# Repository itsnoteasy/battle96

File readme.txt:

this is a work in progress keyboard, not ready for use in a build.

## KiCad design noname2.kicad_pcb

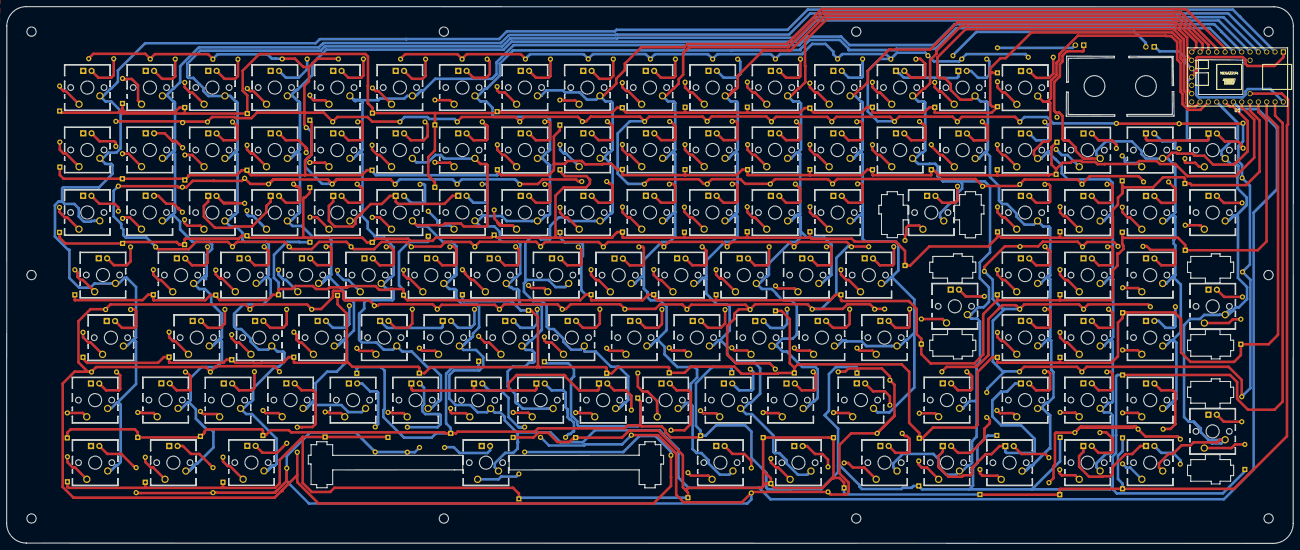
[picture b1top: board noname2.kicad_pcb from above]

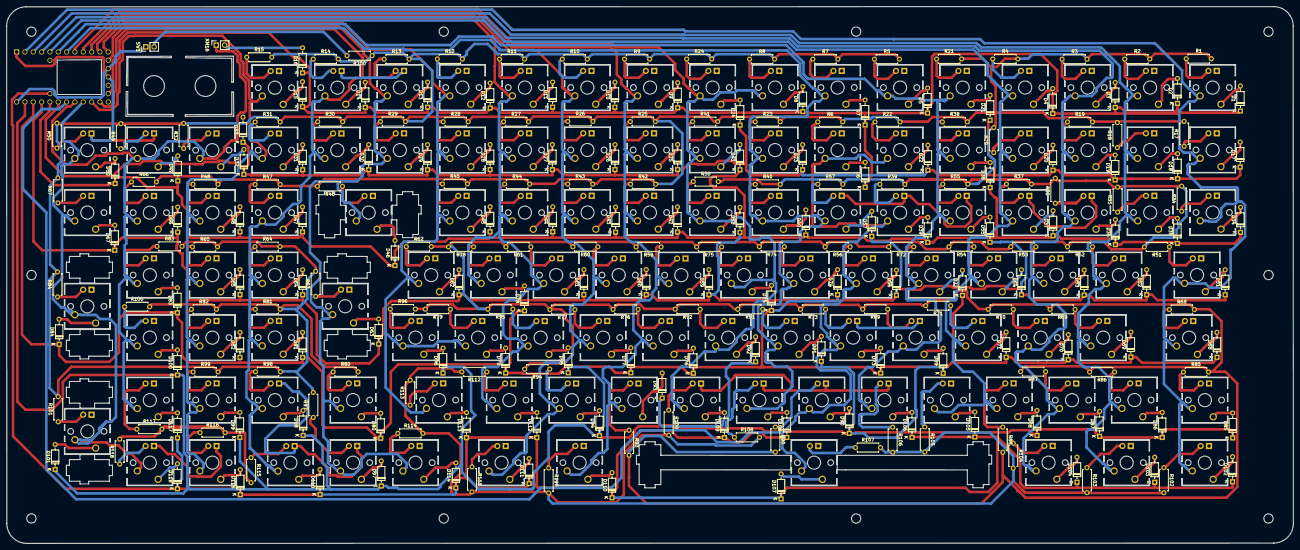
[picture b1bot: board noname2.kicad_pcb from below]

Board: 2 copper layers, 392.1 x 163.5 mm, 354 parts (237 on the bottom side), 262 nets.

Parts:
D1, D2, D3, D4, D5, D6, D7, D8, D9, D10, D11, D12, D13, D14, D15, D16, D17, D18, D19, D20, D21, D22, D23, D24, D25, D26, D27, D28, D29, D30, D31, D32, D33, D34, D35, D36, D37, D38, D39, D40, D41, D42, D43, D44, D45, D46, D47, D48, D49, D50, D51, D52, D53, D54, D55, D56, D57, D58, D59, D60, D61, D62, D63, D64, D65, D66, D67, D68, D69, D70, D71, D72, D73, D74, D75, D76, D77, D78, D79, D80, D81, D82, D83, D84, D85, D86, D87, D88, D89, D90, D91, D92, D93, D94, D95, D96, D97, D98, D99, D100, D101, D102, D103, D104, D105, D106, D107, D108, D109, D110, D111, D112, D113, D114, D115, D116, D117, D118: 1N4148; D_DO-35_SOD27_P7.62mm_Horizontal
MX1, MX2, MX3, MX4, MX5, MX6, MX7, MX8, MX9, MX10, MX11, MX12, MX13, MX14, MX15, MX17, MX18, MX19, MX20, MX21, MX22, MX23, MX24, MX25, MX26, MX27, MX28, MX29, MX30, MX31, MX32, MX34, MX35, MX36, MX37, MX38, MX39, MX40, MX41, MX42, MX43, MX44, MX45, MX46, MX47, MX48, MX49, MX50, MX51, MX52, MX53, MX54, MX55, MX56, MX57, MX58, MX59, MX60, MX61, MX62, MX63, MX64, MX65, MX66, MX67, MX68, MX69, MX70, MX71, MX72, MX73, MX74, MX75, MX76, MX77, MX78, MX79, MX80, MX81, MX82, MX83, MX84, MX85, MX86, MX87, MX88, MX89, MX90, MX91, MX92, MX93, MX94, MX95, MX96, MX97, MX98, MX99, MX100, MX101, MX102, MX103, MX104, MX105, MX106, MX107, MX108, MX109, MX110, MX111, MX112, MX113, MX114, MX115, MX116, MX117, MX118: MX-1U; MX_breakout2
R1, R2, R3, R4, R5, R6, R7, R8, R9, R10, R11, R12, R13, R14, R15, R17, R18, R19, R20, R21, R22, R23, R24, R25, R26, R27, R28, R29, R30, R31, R32, R34, R35, R36, R37, R38, R39, R40, R41, R42, R43, R44, R45, R46, R47, R48, R49, R50, R51, R52, R53, R54, R55, R56, R57, R58, R59, R60, R61, R62, R63, R64, R65, R66, R67, R68, R69, R70, R71, R72, R73, R74, R75, R76, R77, R78, R79, R80, R81, R82, R83, R84, R85, R86, R87, R88, R89, R90, R91, R92, R93, R94, R95, R96, R97, R98, R99, R100, R101, R102, R103, R104, R105, R106, R107, R108, R109, R110, R111, R112, R113, R114, R115, R116, R117, R118, R200: R; R_Axial_DIN0207_L6.3mm_D2.5mm_P7.62mm_Horizontal
SW1: SW_SPST; PinHeader_1x02_P2.54mm_Vertical
U1: TEENSY2.0; Teensy2.0
XM16: Conn_01x02_Male; PinSocket_1x02_P2.54mm_Vertical

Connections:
COL0: MX1.1, MX17.1, MX34.1, MX51.1, MX68.1, MX85.1, MX102.1, U1.2
COL1: MX2.1, MX18.1, MX35.1, MX52.1, MX69.1, MX86.1, MX103.1, U1.3
COL2: MX3.1, MX19.1, MX36.1, MX53.1, MX70.1, MX87.1, MX104.1, U1.4
COL3: MX4.1, MX20.1, MX37.1, MX54.1, MX71.1, MX88.1, MX105.1, U1.5
COL4: MX5.1, MX21.1, MX38.1, MX55.1, MX72.1, MX89.1, MX106.1, U1.6
COL5: MX6.1, MX22.1, MX39.1, MX56.1, MX73.1, MX90.1, MX107.1, U1.23
COL6: MX7.1, MX23.1, MX40.1, MX57.1, MX74.1, MX91.1, MX108.1, U1.7
COL7: MX8.1, MX24.1, MX41.1, MX58.1, MX75.1, MX92.1, MX109.1, U1.8
COL8: MX9.1, MX25.1, MX42.1, MX59.1, MX76.1, MX93.1, MX110.1, U1.9
COL9: MX10.1, MX26.1, MX43.1, MX60.1, MX77.1, MX94.1, MX111.1, U1.10
COL10: MX11.1, MX27.1, MX44.1, MX61.1, MX78.1, MX95.1, MX112.1, U1.11
COL11: MX12.1, MX28.1, MX45.1, MX62.1, MX79.1, MX96.1, MX113.1, U1.12
COL12: MX13.1, MX29.1, MX46.1, MX63.1, MX80.1, MX97.1, MX114.1, U1.13
COL13: MX14.1, MX30.1, MX47.1, MX64.1, MX81.1, MX98.1, MX115.1, U1.17
COL14: MX15.1, MX31.1, MX48.1, MX65.1, MX82.1, MX99.1, MX116.1, U1.20
COL15: MX32.1, MX49.1, MX66.1, MX83.1, MX100.1, MX117.1, U1.22, XM16.1
COL16: MX50.1, MX67.1, MX84.1, MX101.1, MX118.1, U1.21
GND: MX1.4, MX2.4, MX3.4, MX4.4, MX5.4, MX6.4, MX7.4, MX8.4, MX9.4, MX10.4, MX11.4, MX12.4, MX13.4, MX14.4, MX15.4, MX17.4, MX18.4, MX19.4, MX20.4, MX21.4, MX22.4, MX23.4, MX24.4, MX25.4, MX26.4, MX27.4, MX28.4, MX29.4, MX30.4, MX31.4, MX32.4, MX34.4, MX35.4, MX36.4, MX37.4, MX38.4, MX39.4, MX40.4, MX41.4, MX42.4, MX43.4, MX44.4, MX45.4, MX46.4, MX47.4, MX48.4, MX49.4, MX50.4, MX51.4, MX52.4, MX53.4, MX54.4, MX55.4, MX56.4, MX57.4, MX58.4, MX59.4, MX60.4, MX61.4, MX62.4, MX63.4, MX64.4, MX65.4, MX66.4, MX67.4, MX68.4, MX69.4, MX70.4, MX71.4, MX72.4, MX73.4, MX74.4, MX75.4, MX76.4, MX77.4, MX78.4, MX79.4, MX80.4, MX81.4, MX82.4, MX83.4, MX84.4, MX85.4, MX86.4, MX87.4, MX88.4, MX89.4, MX90.4, MX91.4, MX92.4, MX93.4, MX94.4, MX95.4, MX96.4, MX97.4, MX98.4, MX99.4, MX100.4, MX101.4, MX102.4, MX103.4, MX104.4, MX105.4, MX106.4, MX107.4, MX108.4, MX109.4, MX110.4, MX111.4, MX112.4, MX113.4, MX114.4, MX115.4, MX116.4, MX117.4, MX118.4, U1.1, U1.15
unnamed: D1.2, MX1.2
unnamed: D2.2, MX2.2
unnamed: D3.2, MX3.2
unnamed: D4.2, MX4.2
unnamed: D5.2, MX5.2
unnamed: D6.2, MX6.2
unnamed: D7.2, MX7.2
unnamed: D8.2, MX8.2
unnamed: D9.2, MX9.2
unnamed: D10.2, MX10.2
unnamed: D11.2, MX11.2
unnamed: D12.2, MX12.2
unnamed: D13.2, MX13.2
unnamed: D14.2, MX14.2
unnamed: D15.2, MX15.2
unnamed: D16.2, XM16.2
unnamed: D17.2, MX17.2
unnamed: D18.2, MX18.2
unnamed: D19.2, MX19.2
unnamed: D20.2, MX20.2
unnamed: D21.2, MX21.2
unnamed: D22.2, MX22.2
unnamed: D23.2, MX23.2
unnamed: D24.2, MX24.2
unnamed: D25.2, MX25.2
unnamed: D26.2, MX26.2
unnamed: D27.2, MX27.2
unnamed: D28.2, MX28.2
unnamed: D29.2, MX29.2
unnamed: D30.2, MX30.2
unnamed: D31.2, MX31.2
unnamed: D32.2, MX32.2
unnamed: D34.2, MX34.2
unnamed: D35.2, MX35.2
unnamed: D36.2, MX36.2
unnamed: D37.2, MX37.2
unnamed: D38.2, MX38.2
unnamed: D39.2, MX39.2
unnamed: D40.2, MX40.2
unnamed: D41.2, MX41.2
unnamed: D42.2, MX42.2
unnamed: D43.2, MX43.2
unnamed: D44.2, MX44.2
unnamed: D45.2, MX45.2
unnamed: D46.2, MX46.2
unnamed: D47.2, MX47.2
unnamed: D48.2, MX48.2
unnamed: D49.2, MX49.2
unnamed: D50.2, MX50.2
unnamed: D51.2, MX51.2
unnamed: D52.2, MX52.2
unnamed: D53.2, MX53.2
unnamed: D54.2, MX54.2
unnamed: D55.2, MX55.2
unnamed: D56.2, MX56.2
unnamed: D57.2, MX57.2
unnamed: D58.2, MX58.2
unnamed: D59.2, MX59.2
unnamed: D60.2, MX60.2
unnamed: D61.2, MX61.2
unnamed: D62.2, MX62.2
unnamed: D63.2, MX63.2
unnamed: D64.2, MX64.2
unnamed: D65.2, MX65.2
unnamed: D66.2, MX66.2
unnamed: D67.2, MX67.2
unnamed: D68.2, MX68.2
unnamed: D69.2, MX69.2
unnamed: D70.2, MX70.2
unnamed: D71.2, MX71.2
unnamed: D72.2, MX72.2
unnamed: D73.2, MX73.2
unnamed: D74.2, MX74.2
unnamed: D75.2, MX75.2
unnamed: D76.2, MX76.2
unnamed: D77.2, MX77.2
unnamed: D78.2, MX78.2
unnamed: D79.2, MX79.2
unnamed: D80.2, MX80.2
unnamed: D81.2, MX81.2
unnamed: D82.2, MX82.2
unnamed: D83.2, MX83.2
unnamed: D84.2, MX84.2
unnamed: D85.2, MX85.2
unnamed: D86.2, MX86.2
unnamed: D87.2, MX87.2
unnamed: D88.2, MX88.2
unnamed: D89.2, MX89.2
unnamed: D90.2, MX90.2
unnamed: D91.2, MX91.2
unnamed: D92.2, MX92.2
unnamed: D93.2, MX93.2
unnamed: D94.2, MX94.2
unnamed: D95.2, MX95.2
unnamed: D96.2, MX96.2
unnamed: D97.2, MX97.2
unnamed: D98.2, MX98.2
unnamed: D99.2, MX99.2
unnamed: D100.2, MX100.2
unnamed: D101.2, MX101.2
unnamed: D102.2, MX102.2
unnamed: D103.2, MX103.2
unnamed: D104.2, MX104.2
unnamed: D105.2, MX105.2
unnamed: D106.2, MX106.2
unnamed: D107.2, MX107.2
unnamed: D108.2, MX108.2
unnamed: D109.2, MX109.2
unnamed: D110.2, MX110.2
unnamed: D111.2, MX111.2
unnamed: D112.2, MX112.2
unnamed: D113.2, MX113.2
unnamed: D114.2, MX114.2
unnamed: D115.2, MX115.2
unnamed: D116.2, MX116.2
unnamed: D117.2, MX117.2
unnamed: D118.2, MX118.2
unnamed: MX1.3, R1.1
unnamed: MX2.3, R2.1
unnamed: MX3.3, R3.1
unnamed: MX4.3, R4.1
unnamed: MX5.3, R5.1
unnamed: MX6.3, R6.1
unnamed: MX7.3, R7.1
unnamed: MX8.3, R8.1
unnamed: MX9.3, R9.1
unnamed: MX10.3, R10.1
unnamed: MX11.3, R11.1
unnamed: MX12.3, R12.1
unnamed: MX13.3, R13.1
unnamed: MX14.3, R14.1
unnamed: MX15.3, R15.1
unnamed: MX17.3, R17.1
unnamed: MX18.3, R18.1
unnamed: MX19.3, R19.1
unnamed: MX20.3, R20.1
unnamed: MX21.3, R21.1
unnamed: MX22.3, R22.1
unnamed: MX23.3, R23.1
unnamed: MX24.3, R24.1
unnamed: MX25.3, R25.1
unnamed: MX26.3, R26.1
unnamed: MX27.3, R27.1
unnamed: MX28.3, R28.1
unnamed: MX29.3, R29.1
unnamed: MX30.3, R30.1
unnamed: MX31.3, R31.1
unnamed: MX32.3, R32.1
unnamed: MX34.3, R34.1
unnamed: MX35.3, R35.1
unnamed: MX36.3, R36.1
unnamed: MX37.3, R37.1
unnamed: MX38.3, R38.1
unnamed: MX39.3, R39.1
unnamed: MX40.3, R40.1
unnamed: MX41.3, R41.1
unnamed: MX42.3, R42.1
unnamed: MX43.3, R43.1
unnamed: MX44.3, R44.1
unnamed: MX45.3, R45.1
unnamed: MX46.3, R46.1
unnamed: MX47.3, R47.1
unnamed: MX48.3, R48.1
unnamed: MX49.3, R49.1
unnamed: MX50.3, R50.1
unnamed: MX51.3, R51.1
unnamed: MX52.3, R52.1
unnamed: MX53.3, R53.1
unnamed: MX54.3, R54.1
unnamed: MX55.3, R55.1
unnamed: MX56.3, R56.1
unnamed: MX57.3, R57.1
unnamed: MX58.3, R58.1
unnamed: MX59.3, R59.1
unnamed: MX60.3, R60.1
unnamed: MX61.3, R61.1
unnamed: MX62.3, R62.1
unnamed: MX63.3, R63.1
unnamed: MX64.3, R64.1
unnamed: MX65.3, R65.1
unnamed: MX66.3, R66.1
unnamed: MX67.3, R67.1
unnamed: MX68.3, R68.1
unnamed: MX69.3, R69.1
unnamed: MX70.3, R70.1
unnamed: MX71.3, R71.1
unnamed: MX72.3, R72.1
unnamed: MX73.3, R73.1
unnamed: MX74.3, R74.1
unnamed: MX75.3, R75.1
unnamed: MX76.3, R76.1
unnamed: MX77.3, R77.1
unnamed: MX78.3, R78.1
unnamed: MX79.3, R79.1
unnamed: MX80.3, R80.1
unnamed: MX81.3, R81.1
unnamed: MX82.3, R82.1
unnamed: MX83.3, R83.1
unnamed: MX84.3, R84.1
unnamed: MX85.3, R85.1
unnamed: MX86.3, R86.1
unnamed: MX87.3, R87.1
unnamed: MX88.3, R88.1
unnamed: MX89.3, R89.1
unnamed: MX90.3, R90.1
unnamed: MX91.3, R91.1
unnamed: MX92.3, R92.1
unnamed: MX93.3, R93.1
unnamed: MX94.3, R94.1
unnamed: MX95.3, R95.1
unnamed: MX96.3, R96.1
unnamed: MX97.3, R97.1
unnamed: MX98.3, R98.1
unnamed: MX99.3, R99.1
unnamed: MX100.3, R100.1
unnamed: MX101.3, R101.1
unnamed: MX102.3, R102.1
unnamed: MX103.3, R103.1
unnamed: MX104.3, R104.1
unnamed: MX105.3, R105.1
unnamed: MX106.3, R106.1
unnamed: MX107.3, R107.1
unnamed: MX108.3, R108.1
unnamed: MX109.3, R109.1
unnamed: MX110.3, R110.1
unnamed: MX111.3, R111.1
unnamed: MX112.3, R112.1
unnamed: MX113.3, R113.1
unnamed: MX114.3, R114.1
unnamed: MX115.3, R115.1
unnamed: MX116.3, R116.1
unnamed: MX117.3, R117.1
unnamed: MX118.3, R118.1
unnamed: R1.2, R2.2, R3.2, R4.2, R5.2, R6.2, R7.2, R8.2, R9.2, R10.2, R11.2, R12.2, R13.2, R14.2, R15.2, R17.2, R18.2, R19.2, R20.2, R21.2, R22.2, R23.2, R24.2, R25.2, R26.2, R27.2, R28.2, R29.2, R30.2, R31.2, R32.2, R34.2, R35.2, R36.2, R37.2, R38.2, R39.2, R40.2, R41.2, R42.2, R43.2, R44.2, R45.2, R46.2, R47.2, R48.2, R49.2, R50.2, R51.2, R52.2, R53.2, R54.2, R55.2, R56.2, R57.2, R58.2, R59.2, R60.2, R61.2, R62.2, R63.2, R64.2, R65.2, R66.2, R67.2, R68.2, R69.2, R70.2, R71.2, R72.2, R73.2, R74.2, R75.2, R76.2, R77.2, R78.2, R79.2, R80.2, R81.2, R82.2, R83.2, R84.2, R85.2, R86.2, R87.2, R88.2, R89.2, R90.2, R91.2, R92.2, R93.2, R94.2, R95.2, R96.2, R97.2, R98.2, R99.2, R100.2, R101.2, R200.1
unnamed: R102.2, R103.2, R104.2, R105.2, R106.2, R107.2, R108.2, R109.2, R110.2, R111.2, R112.2, R113.2, R114.2, R115.2, R116.2, R117.2, R118.2
unnamed: R200.2, SW1.2
ROW0: D1.1, D2.1, D3.1, D4.1, D5.1, D6.1, D7.1, D8.1, D9.1, D10.1, D11.1, D12.1, D13.1, D14.1, D15.1, D16.1, U1.19
ROW1: D17.1, D18.1, D19.1, D20.1, D21.1, D22.1, D23.1, D24.1, D25.1, D26.1, D27.1, D28.1, D29.1, D30.1, D31.1, D32.1, D33.1, U1.24
ROW2: D34.1, D35.1, D36.1, D37.1, D38.1, D39.1, D40.1, D41.1, D42.1, D43.1, D44.1, D45.1, D46.1, D47.1, D48.1, D49.1, D50.1, U1.25
ROW3: D51.1, D52.1, D53.1, D54.1, D55.1, D56.1, D57.1, D58.1, D59.1, D60.1, D61.1, D62.1, D63.1, D64.1, D65.1, D66.1, D67.1, U1.26
ROW4: D68.1, D69.1, D70.1, D71.1, D72.1, D73.1, D74.1, D75.1, D76.1, D77.1, D78.1, D79.1, D80.1, D81.1, D82.1, D83.1, D84.1, U1.27
ROW5: D85.1, D86.1, D87.1, D88.1, D89.1, D90.1, D91.1, D92.1, D93.1, D94.1, D95.1, D96.1, D97.1, D98.1, D99.1, D100.1, D101.1, U1.28
ROW6: D102.1, D103.1, D104.1, D105.1, D106.1, D107.1, D108.1, D109.1, D110.1, D111.1, D112.1, D113.1, D114.1, D115.1, D116.1, D117.1, D118.1, U1.31
VCC: SW1.1, U1.14, U1.29
